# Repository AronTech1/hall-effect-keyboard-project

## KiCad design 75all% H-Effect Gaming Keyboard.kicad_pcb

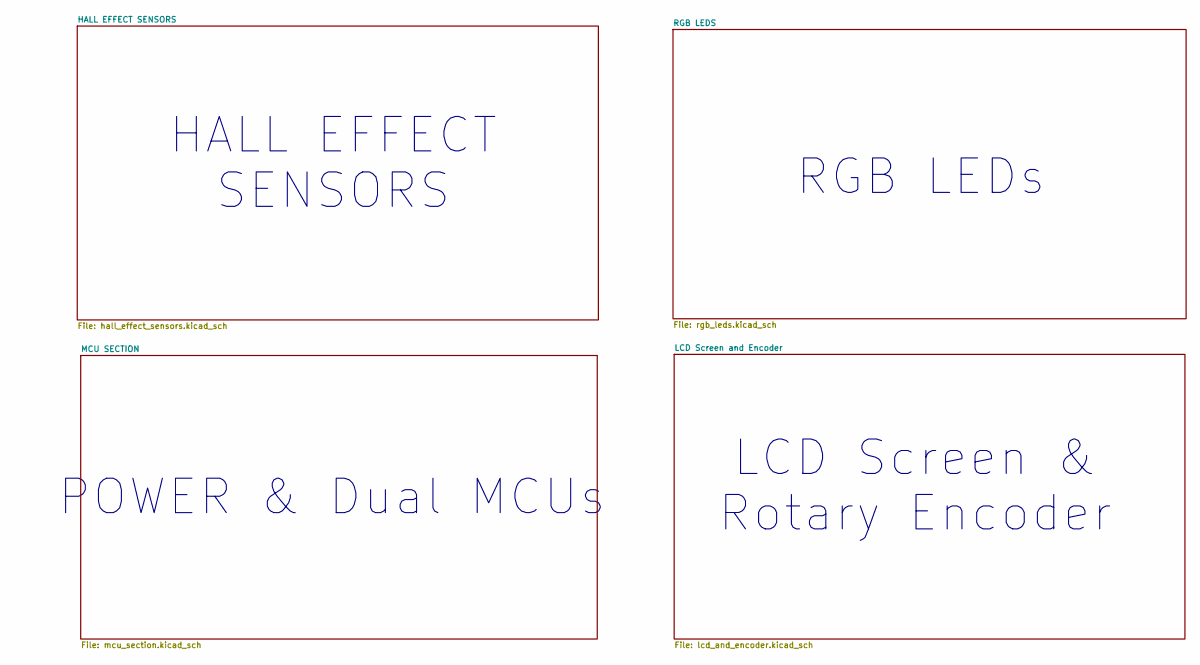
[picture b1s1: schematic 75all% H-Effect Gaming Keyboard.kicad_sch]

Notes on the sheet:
LCD Screen & Rotary Encoder
HALL EFFECT SENSORS
POWER & Dual MCUs
RGB LEDs

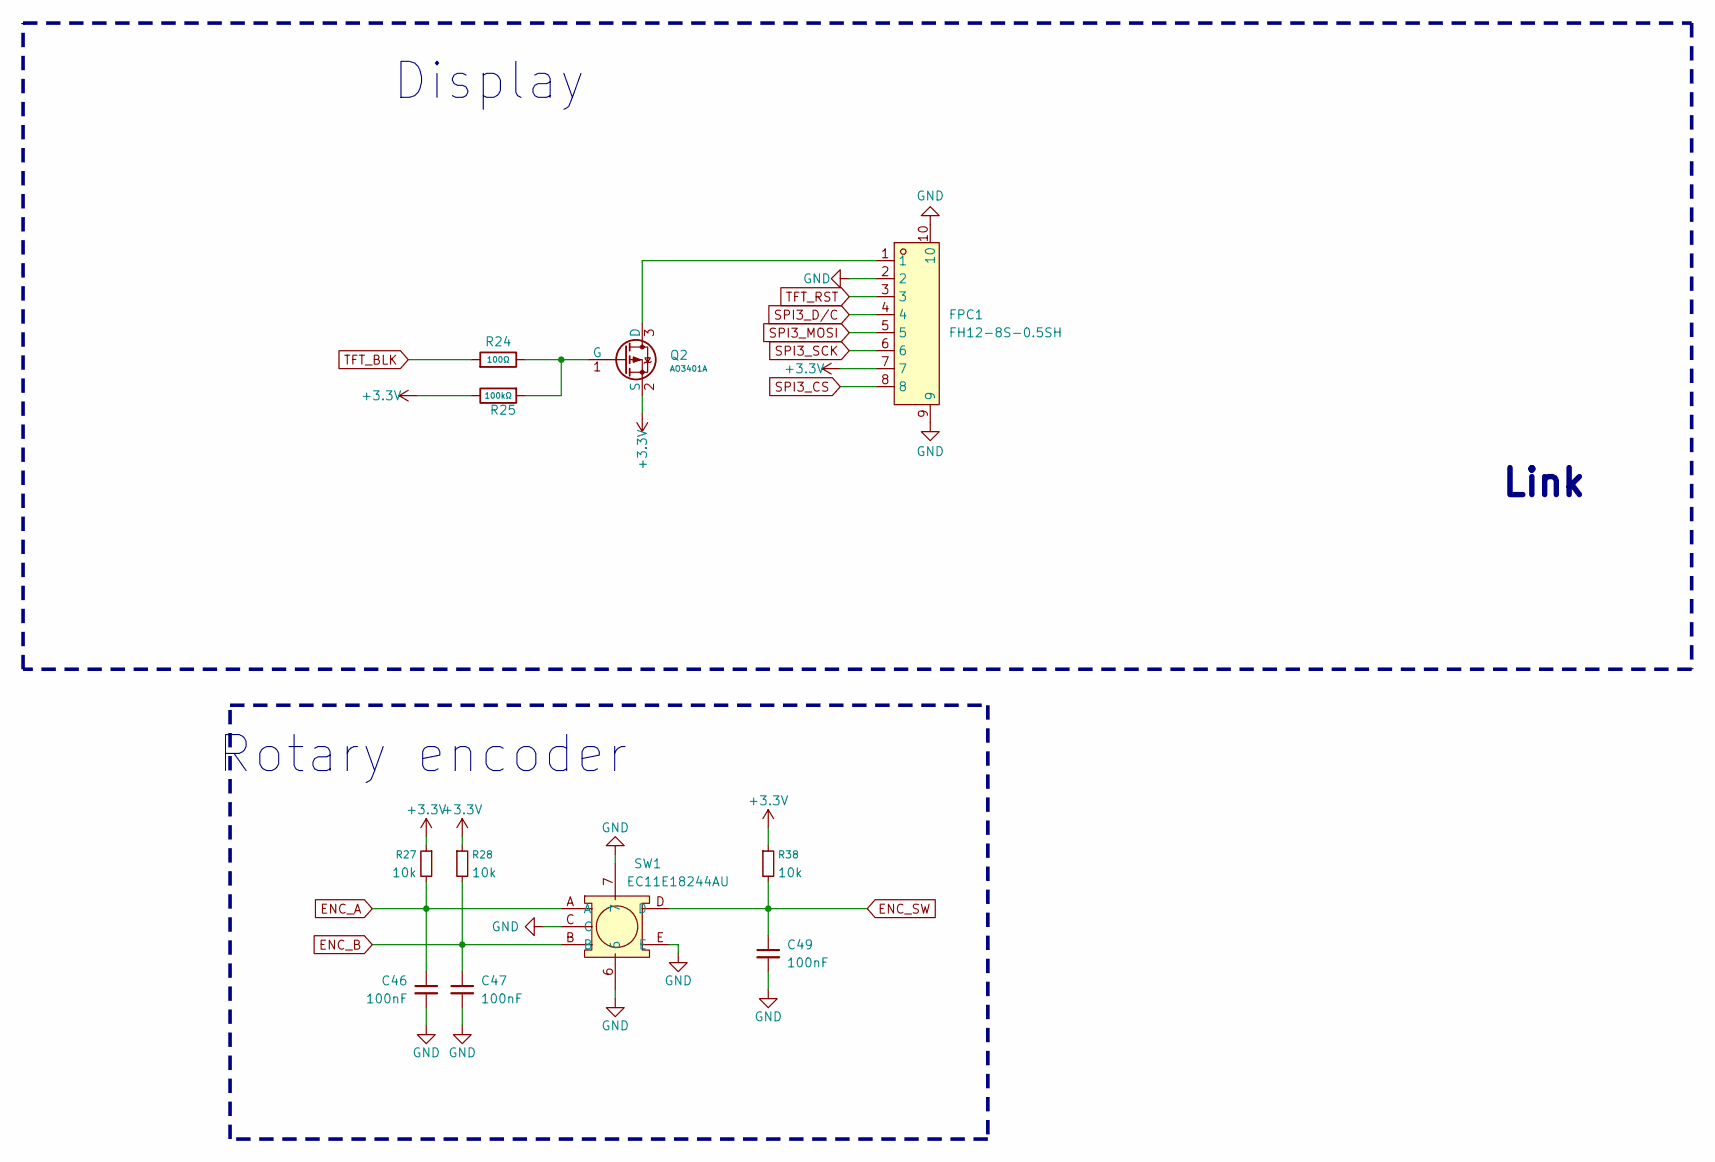
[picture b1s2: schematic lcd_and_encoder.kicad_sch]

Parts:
C46, C47, C49: 100nF; C_0402_1005Metric; JLCPCB Part # C307331
FPC1: FH12-8S-0.5SH; FPC-SMD_8P-P0.50_FH12S-8S-0.5SH-55; MPN FH12-8S-0.5SH(55); LCSC Part C597995
Q2: AO3401A; Q_SOT-23; Part AO3401A; LCSC C15127
R24: 100Ω; R_0603; Overload Voltage (Max) 75V; Tolerance ±1%; Part 0603WAF1000T5E; LCSC C22775
R25: 100kΩ; R_0603; Overload Voltage (Max) 75V; Tolerance ±1%; Part 0603WAF1003T5E; LCSC C25803
R27, R28, R38: 10k; R_0402_1005Metric; JLCPCB Part # C173683
SW1: EC11E18244AU; SW-TH_EC11XXXXXXXX; MPN EC11E18244AU; JLCPCB Part # C202365

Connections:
+3.3V: FPC1.7, Q2.2 (S), R25.2, R27.1, R28.1, R38.1; also elsewhere on the board
ENC_A: C46.1, R27.2, SW1.A; also elsewhere on the board
ENC_B: C47.1, R28.2, SW1.B; also elsewhere on the board
ENC_SW: C49.1, R38.2, SW1.D; also elsewhere on the board
GND: C46.2, C47.2, C49.2, FPC1.2, FPC1.9, FPC1.10, SW1.6, SW1.7, SW1.C, SW1.E; also elsewhere on the board
unnamed: FPC1.1, Q2.3 (D)
unnamed: Q2.1 (G), R24.2, R25.1
SPI3_CS: FPC1.8; also elsewhere on the board
SPI3_D/C: FPC1.4; also elsewhere on the board
SPI3_MOSI: FPC1.5; also elsewhere on the board
SPI3_SCK: FPC1.6; also elsewhere on the board
TFT_BLK: R24.1; also elsewhere on the board
TFT_RST: FPC1.3; also elsewhere on the board

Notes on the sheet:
Link
Display
Rotary encoder

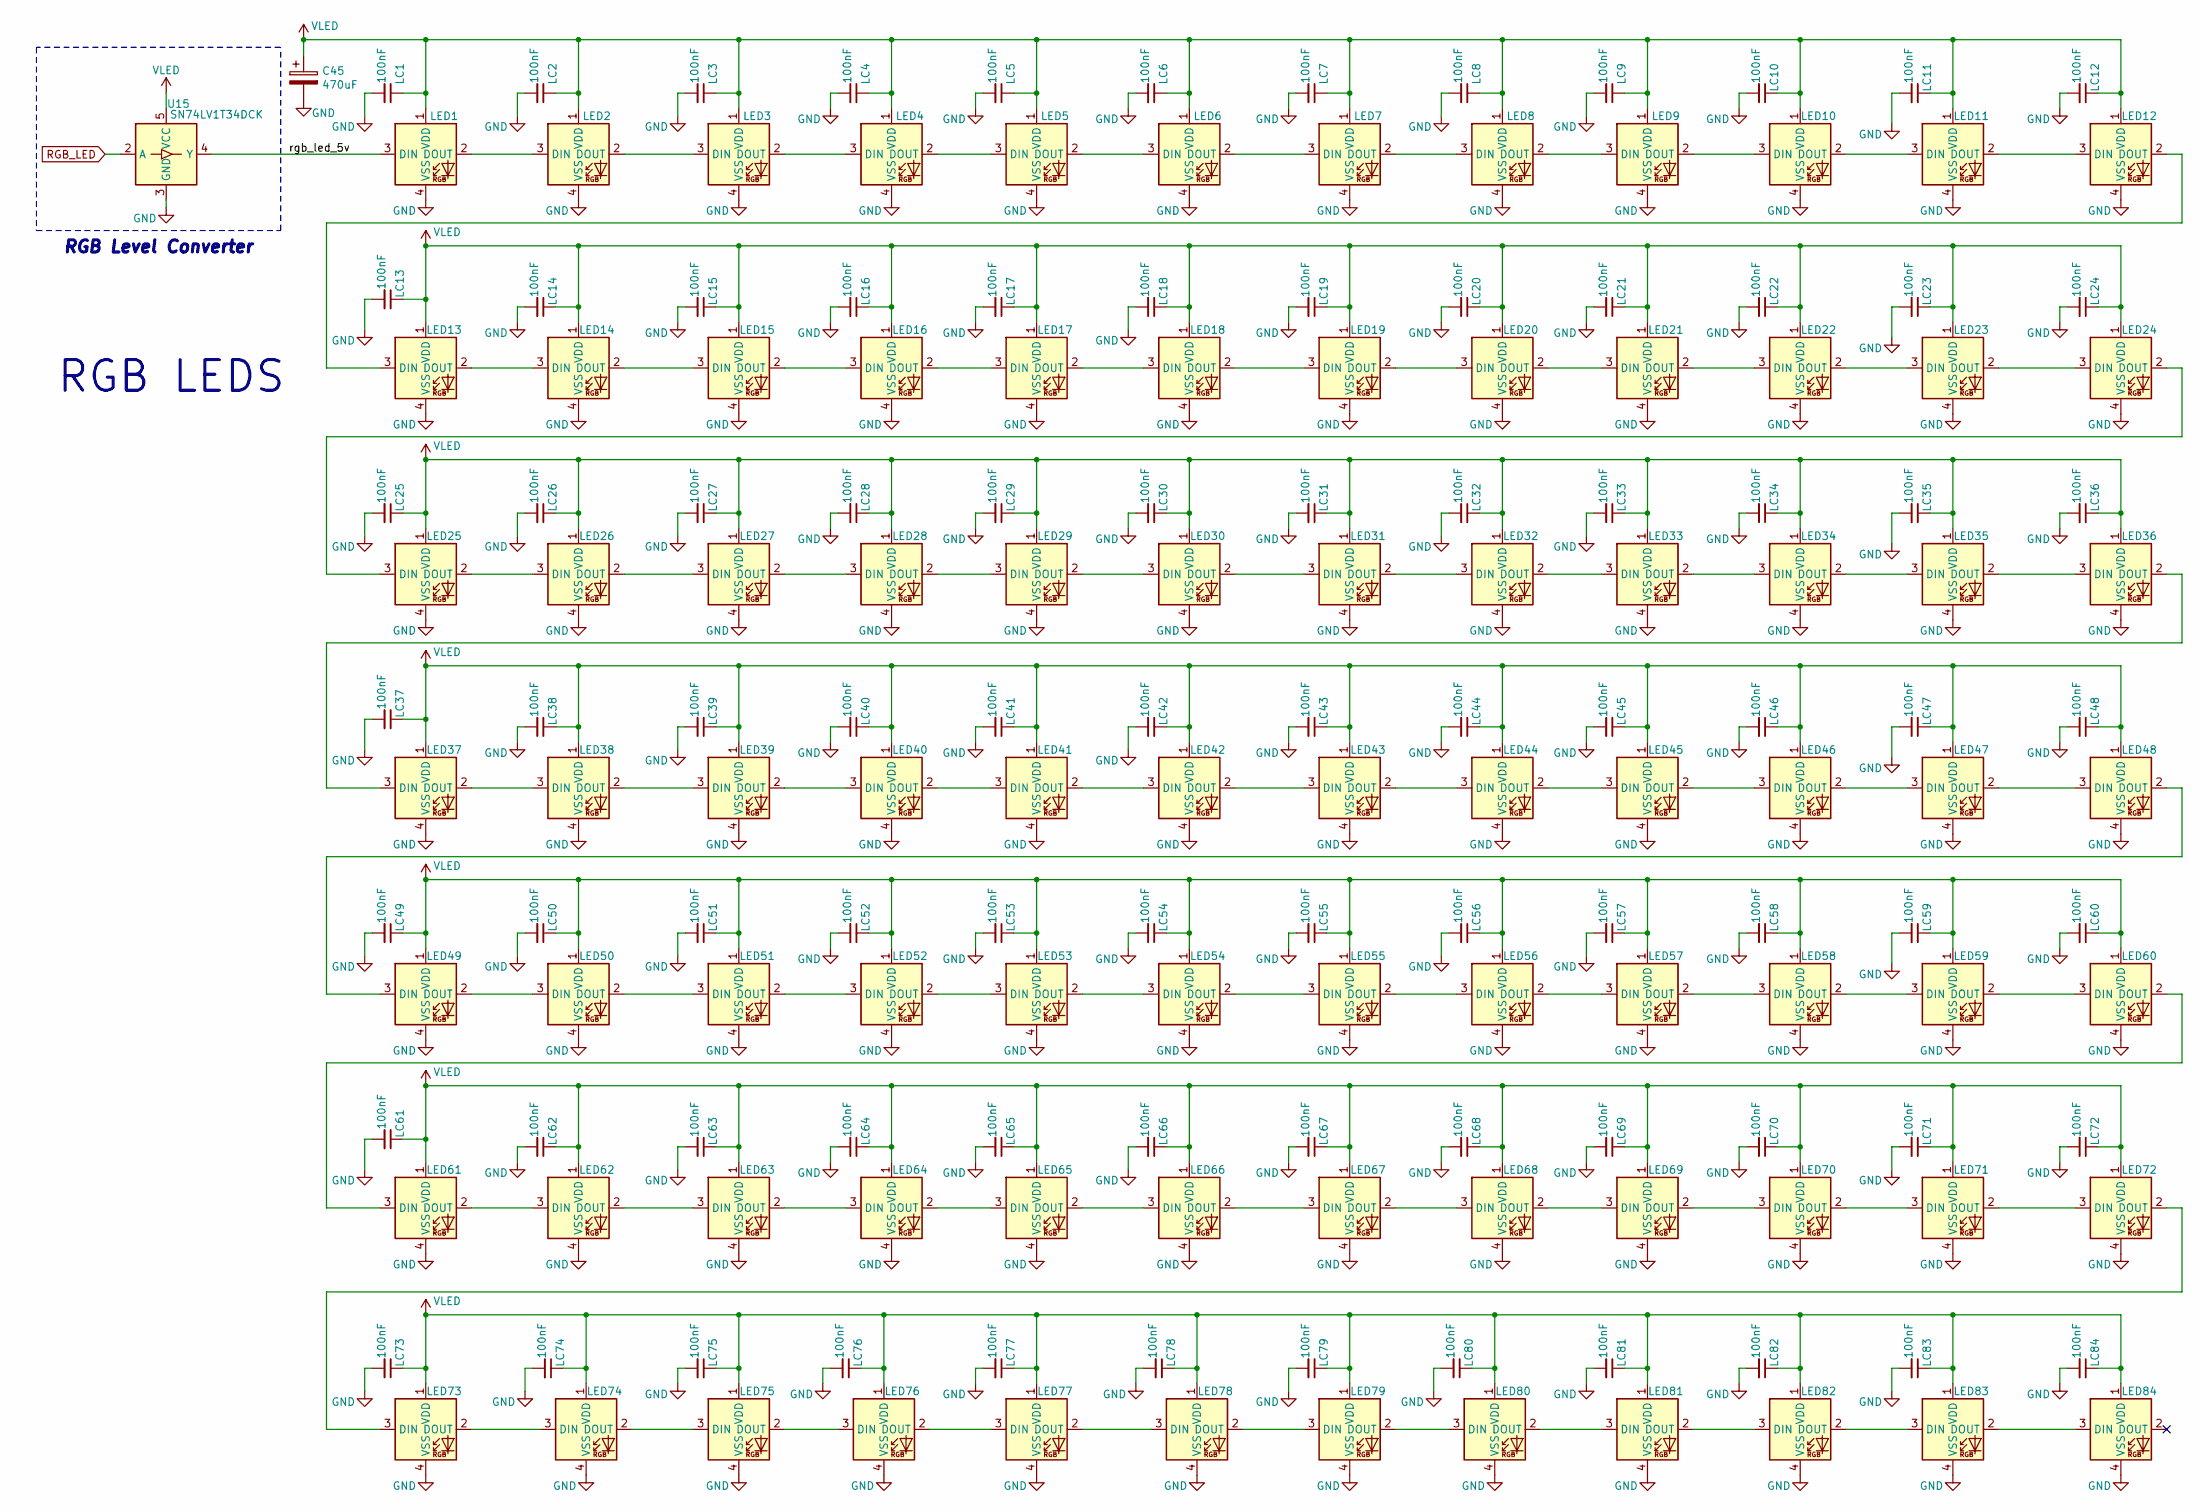
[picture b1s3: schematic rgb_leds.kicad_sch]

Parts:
C45: 470uF; CP_EIA-7343-31_Kemet-D; MFR.Part # TAJD477K006RNJ; JLCPCB Part # C7229
LC1, LC2, LC3, LC4, LC5, LC6, LC7, LC8, LC9, LC10, LC11, LC12, LC13, LC14, LC15, LC16, LC17, LC18, LC19, LC20, LC21, LC22, LC23, LC24, LC25, LC26, LC27, LC28, LC29, LC30, LC31, LC32, LC33, LC34, LC35, LC36, LC37, LC38, LC39, LC40, LC41, LC42, LC43, LC44, LC45, LC46, LC47, LC48, LC49, LC50, LC51, LC52, LC53, LC54, LC55, LC56, LC57, LC58, LC59, LC60, LC61, LC62, LC63, LC64, LC65, LC66, LC67, LC68, LC69, LC70, LC71, LC72, LC73, LC74, LC75, LC76, LC77, LC78, LC79, LC80, LC81, LC82, LC83, LC84: 100nF; C_0402_1005Metric; LCSC C1525
LED1, LED2, LED3, LED4, LED5, LED6, LED7, LED8, LED9, LED10, LED11, LED12, LED13, LED14, LED15, LED16, LED17, LED18, LED19, LED20, LED21, LED22, LED23, LED24, LED25, LED26, LED27, LED28, LED29, LED30, LED31, LED32, LED33, LED34, LED35, LED36, LED37, LED38, LED39, LED40, LED41, LED42, LED43, LED44, LED45, LED46, LED47, LED48, LED49, LED50, LED51, LED52, LED53, LED54, LED55, LED56, LED57, LED58, LED59, LED60, LED61, LED62, LED63, LED64, LED65, LED66, LED67, LED68, LED69, LED70, LED71, LED72, LED73, LED74, LED75, LED76, LED77, LED78, LED79, LED80, LED81, LED82, LED83, LED84: MX_SK6812MINI-E; LED_MX_6028R; LCSC C5149201
U15: SN74LV1T34DCK; SOT-353_SC-70-5; LCSC C48543212

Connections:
/RGB LEDS/rgb_led_5v: LED1.3 (DIN), U15.4 (Y)
GND: C45.2, LC1.2, LC2.2, LC3.2, LC4.2, LC5.2, LC6.2, LC7.2, LC8.2, LC9.2, LC10.2, LC11.2, LC12.2, LC13.2, LC14.2, LC15.2, LC16.2, LC17.2, LC18.2, LC19.2, LC20.2, LC21.2, LC22.2, LC23.2, LC24.2, LC25.2, LC26.2, LC27.2, LC28.2, LC29.2, LC30.2, LC31.2, LC32.2, LC33.2, LC34.2, LC35.2, LC36.2, LC37.2, LC38.2, LC39.2, LC40.2, LC41.2, LC42.2, LC43.2, LC44.2, LC45.2, LC46.2, LC47.2, LC48.2, LC49.2, LC50.2, LC51.2, LC52.2, LC53.2, LC54.2, LC55.2, LC56.2, LC57.2, LC58.2, LC59.2, LC60.2, LC61.2, LC62.2, LC63.2, LC64.2, LC65.2, LC66.2, LC67.2, LC68.2, LC69.2, LC70.2, LC71.2, LC72.2, LC73.2, LC74.2, LC75.2, LC76.2, LC77.2, LC78.2, LC79.2, LC80.2, LC81.2, LC82.2, LC83.2, LC84.2, LED1.4 (VSS), LED2.4 (VSS), LED3.4 (VSS), LED4.4 (VSS), LED5.4 (VSS), LED6.4 (VSS), LED7.4 (VSS), LED8.4 (VSS), LED9.4 (VSS), LED10.4 (VSS), LED11.4 (VSS), LED12.4 (VSS), LED13.4 (VSS), LED14.4 (VSS), LED15.4 (VSS), LED16.4 (VSS), LED17.4 (VSS), LED18.4 (VSS), LED19.4 (VSS), LED20.4 (VSS), LED21.4 (VSS), LED22.4 (VSS), LED23.4 (VSS), LED24.4 (VSS), LED25.4 (VSS), LED26.4 (VSS), LED27.4 (VSS), LED28.4 (VSS), LED29.4 (VSS), LED30.4 (VSS), LED31.4 (VSS), LED32.4 (VSS), LED33.4 (VSS), LED34.4 (VSS), LED35.4 (VSS), LED36.4 (VSS), LED37.4 (VSS), LED38.4 (VSS), LED39.4 (VSS), LED40.4 (VSS), LED41.4 (VSS), LED42.4 (VSS), LED43.4 (VSS), LED44.4 (VSS), LED45.4 (VSS), LED46.4 (VSS), LED47.4 (VSS), LED48.4 (VSS), LED49.4 (VSS), LED50.4 (VSS), LED51.4 (VSS), LED52.4 (VSS), LED53.4 (VSS), LED54.4 (VSS), LED55.4 (VSS), LED56.4 (VSS), LED57.4 (VSS), LED58.4 (VSS), LED59.4 (VSS), LED60.4 (VSS), LED61.4 (VSS), LED62.4 (VSS), LED63.4 (VSS), LED64.4 (VSS), LED65.4 (VSS), LED66.4 (VSS), LED67.4 (VSS), LED68.4 (VSS), LED69.4 (VSS), LED70.4 (VSS), LED71.4 (VSS), LED72.4 (VSS), LED73.4 (VSS), LED74.4 (VSS), LED75.4 (VSS), LED76.4 (VSS), LED77.4 (VSS), LED78.4 (VSS), LED79.4 (VSS), LED80.4 (VSS), LED81.4 (VSS), LED82.4 (VSS), LED83.4 (VSS), LED84.4 (VSS), U15.3 (GND); also elsewhere on the board
unnamed: LED1.2 (DOUT), LED2.3 (DIN)
unnamed: LED2.2 (DOUT), LED3.3 (DIN)
unnamed: LED3.2 (DOUT), LED4.3 (DIN)
unnamed: LED4.2 (DOUT), LED5.3 (DIN)
unnamed: LED5.2 (DOUT), LED6.3 (DIN)
unnamed: LED6.2 (DOUT), LED7.3 (DIN)
unnamed: LED7.2 (DOUT), LED8.3 (DIN)
unnamed: LED8.2 (DOUT), LED9.3 (DIN)
unnamed: LED9.2 (DOUT), LED10.3 (DIN)
unnamed: LED10.2 (DOUT), LED11.3 (DIN)
unnamed: LED11.2 (DOUT), LED12.3 (DIN)
unnamed: LED12.2 (DOUT), LED13.3 (DIN)
unnamed: LED13.2 (DOUT), LED14.3 (DIN)
unnamed: LED14.2 (DOUT), LED15.3 (DIN)
unnamed: LED15.2 (DOUT), LED16.3 (DIN)
unnamed: LED16.2 (DOUT), LED17.3 (DIN)
unnamed: LED17.2 (DOUT), LED18.3 (DIN)
unnamed: LED18.2 (DOUT), LED19.3 (DIN)
unnamed: LED19.2 (DOUT), LED20.3 (DIN)
unnamed: LED20.2 (DOUT), LED21.3 (DIN)
unnamed: LED21.2 (DOUT), LED22.3 (DIN)
unnamed: LED22.2 (DOUT), LED23.3 (DIN)
unnamed: LED23.2 (DOUT), LED24.3 (DIN)
unnamed: LED24.2 (DOUT), LED25.3 (DIN)
unnamed: LED25.2 (DOUT), LED26.3 (DIN)
unnamed: LED26.2 (DOUT), LED27.3 (DIN)
unnamed: LED27.2 (DOUT), LED28.3 (DIN)
unnamed: LED28.2 (DOUT), LED29.3 (DIN)
unnamed: LED29.2 (DOUT), LED30.3 (DIN)
unnamed: LED30.2 (DOUT), LED31.3 (DIN)
unnamed: LED31.2 (DOUT), LED32.3 (DIN)
unnamed: LED32.2 (DOUT), LED33.3 (DIN)
unnamed: LED33.2 (DOUT), LED34.3 (DIN)
unnamed: LED34.2 (DOUT), LED35.3 (DIN)
unnamed: LED35.2 (DOUT), LED36.3 (DIN)
unnamed: LED36.2 (DOUT), LED37.3 (DIN)
unnamed: LED37.2 (DOUT), LED38.3 (DIN)
unnamed: LED38.2 (DOUT), LED39.3 (DIN)
unnamed: LED39.2 (DOUT), LED40.3 (DIN)
unnamed: LED40.2 (DOUT), LED41.3 (DIN)
unnamed: LED41.2 (DOUT), LED42.3 (DIN)
unnamed: LED42.2 (DOUT), LED43.3 (DIN)
unnamed: LED43.2 (DOUT), LED44.3 (DIN)
unnamed: LED44.2 (DOUT), LED45.3 (DIN)
unnamed: LED45.2 (DOUT), LED46.3 (DIN)
unnamed: LED46.2 (DOUT), LED47.3 (DIN)
unnamed: LED47.2 (DOUT), LED48.3 (DIN)
unnamed: LED48.2 (DOUT), LED49.3 (DIN)
unnamed: LED49.2 (DOUT), LED50.3 (DIN)
unnamed: LED50.2 (DOUT), LED51.3 (DIN)
unnamed: LED51.2 (DOUT), LED52.3 (DIN)
unnamed: LED52.2 (DOUT), LED53.3 (DIN)
unnamed: LED53.2 (DOUT), LED54.3 (DIN)
unnamed: LED54.2 (DOUT), LED55.3 (DIN)
unnamed: LED55.2 (DOUT), LED56.3 (DIN)
unnamed: LED56.2 (DOUT), LED57.3 (DIN)
unnamed: LED57.2 (DOUT), LED58.3 (DIN)
unnamed: LED58.2 (DOUT), LED59.3 (DIN)
unnamed: LED59.2 (DOUT), LED60.3 (DIN)
unnamed: LED60.2 (DOUT), LED61.3 (DIN)
unnamed: LED61.2 (DOUT), LED62.3 (DIN)
unnamed: LED62.2 (DOUT), LED63.3 (DIN)
unnamed: LED63.2 (DOUT), LED64.3 (DIN)
unnamed: LED64.2 (DOUT), LED65.3 (DIN)
unnamed: LED65.2 (DOUT), LED66.3 (DIN)
unnamed: LED66.2 (DOUT), LED67.3 (DIN)
unnamed: LED67.2 (DOUT), LED68.3 (DIN)
unnamed: LED68.2 (DOUT), LED69.3 (DIN)
unnamed: LED69.2 (DOUT), LED70.3 (DIN)
unnamed: LED70.2 (DOUT), LED71.3 (DIN)
unnamed: LED71.2 (DOUT), LED72.3 (DIN)
unnamed: LED72.2 (DOUT), LED73.3 (DIN)
unnamed: LED73.2 (DOUT), LED74.3 (DIN)
unnamed: LED74.2 (DOUT), LED75.3 (DIN)
unnamed: LED75.2 (DOUT), LED76.3 (DIN)
unnamed: LED76.2 (DOUT), LED77.3 (DIN)
unnamed: LED77.2 (DOUT), LED78.3 (DIN)
unnamed: LED78.2 (DOUT), LED79.3 (DIN)
unnamed: LED79.2 (DOUT), LED80.3 (DIN)
unnamed: LED80.2 (DOUT), LED81.3 (DIN)
unnamed: LED81.2 (DOUT), LED82.3 (DIN)
unnamed: LED82.2 (DOUT), LED83.3 (DIN)
unnamed: LED83.2 (DOUT), LED84.3 (DIN)
RGB_LED: U15.2 (A); also elsewhere on the board
VLED: C45.1, LC1.1, LC2.1, LC3.1, LC4.1, LC5.1, LC6.1, LC7.1, LC8.1, LC9.1, LC10.1, LC11.1, LC12.1, LC13.1, LC14.1, LC15.1, LC16.1, LC17.1, LC18.1, LC19.1, LC20.1, LC21.1, LC22.1, LC23.1, LC24.1, LC25.1, LC26.1, LC27.1, LC28.1, LC29.1, LC30.1, LC31.1, LC32.1, LC33.1, LC34.1, LC35.1, LC36.1, LC37.1, LC38.1, LC39.1, LC40.1, LC41.1, LC42.1, LC43.1, LC44.1, LC45.1, LC46.1, LC47.1, LC48.1, LC49.1, LC50.1, LC51.1, LC52.1, LC53.1, LC54.1, LC55.1, LC56.1, LC57.1, LC58.1, LC59.1, LC60.1, LC61.1, LC62.1, LC63.1, LC64.1, LC65.1, LC66.1, LC67.1, LC68.1, LC69.1, LC70.1, LC71.1, LC72.1, LC73.1, LC74.1, LC75.1, LC76.1, LC77.1, LC78.1, LC79.1, LC80.1, LC81.1, LC82.1, LC83.1, LC84.1, LED1.1 (VDD), LED2.1 (VDD), LED3.1 (VDD), LED4.1 (VDD), LED5.1 (VDD), LED6.1 (VDD), LED7.1 (VDD), LED8.1 (VDD), LED9.1 (VDD), LED10.1 (VDD), LED11.1 (VDD), LED12.1 (VDD), LED13.1 (VDD), LED14.1 (VDD), LED15.1 (VDD), LED16.1 (VDD), LED17.1 (VDD), LED18.1 (VDD), LED19.1 (VDD), LED20.1 (VDD), LED21.1 (VDD), LED22.1 (VDD), LED23.1 (VDD), LED24.1 (VDD), LED25.1 (VDD), LED26.1 (VDD), LED27.1 (VDD), LED28.1 (VDD), LED29.1 (VDD), LED30.1 (VDD), LED31.1 (VDD), LED32.1 (VDD), LED33.1 (VDD), LED34.1 (VDD), LED35.1 (VDD), LED36.1 (VDD), LED37.1 (VDD), LED38.1 (VDD), LED39.1 (VDD), LED40.1 (VDD), LED41.1 (VDD), LED42.1 (VDD), LED43.1 (VDD), LED44.1 (VDD), LED45.1 (VDD), LED46.1 (VDD), LED47.1 (VDD), LED48.1 (VDD), LED49.1 (VDD), LED50.1 (VDD), LED51.1 (VDD), LED52.1 (VDD), LED53.1 (VDD), LED54.1 (VDD), LED55.1 (VDD), LED56.1 (VDD), LED57.1 (VDD), LED58.1 (VDD), LED59.1 (VDD), LED60.1 (VDD), LED61.1 (VDD), LED62.1 (VDD), LED63.1 (VDD), LED64.1 (VDD), LED65.1 (VDD), LED66.1 (VDD), LED67.1 (VDD), LED68.1 (VDD), LED69.1 (VDD), LED70.1 (VDD), LED71.1 (VDD), LED72.1 (VDD), LED73.1 (VDD), LED74.1 (VDD), LED75.1 (VDD), LED76.1 (VDD), LED77.1 (VDD), LED78.1 (VDD), LED79.1 (VDD), LED80.1 (VDD), LED81.1 (VDD), LED82.1 (VDD), LED83.1 (VDD), LED84.1 (VDD), U15.5 (VCC); also elsewhere on the board

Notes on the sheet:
RGB Level Converter
RGB LEDS

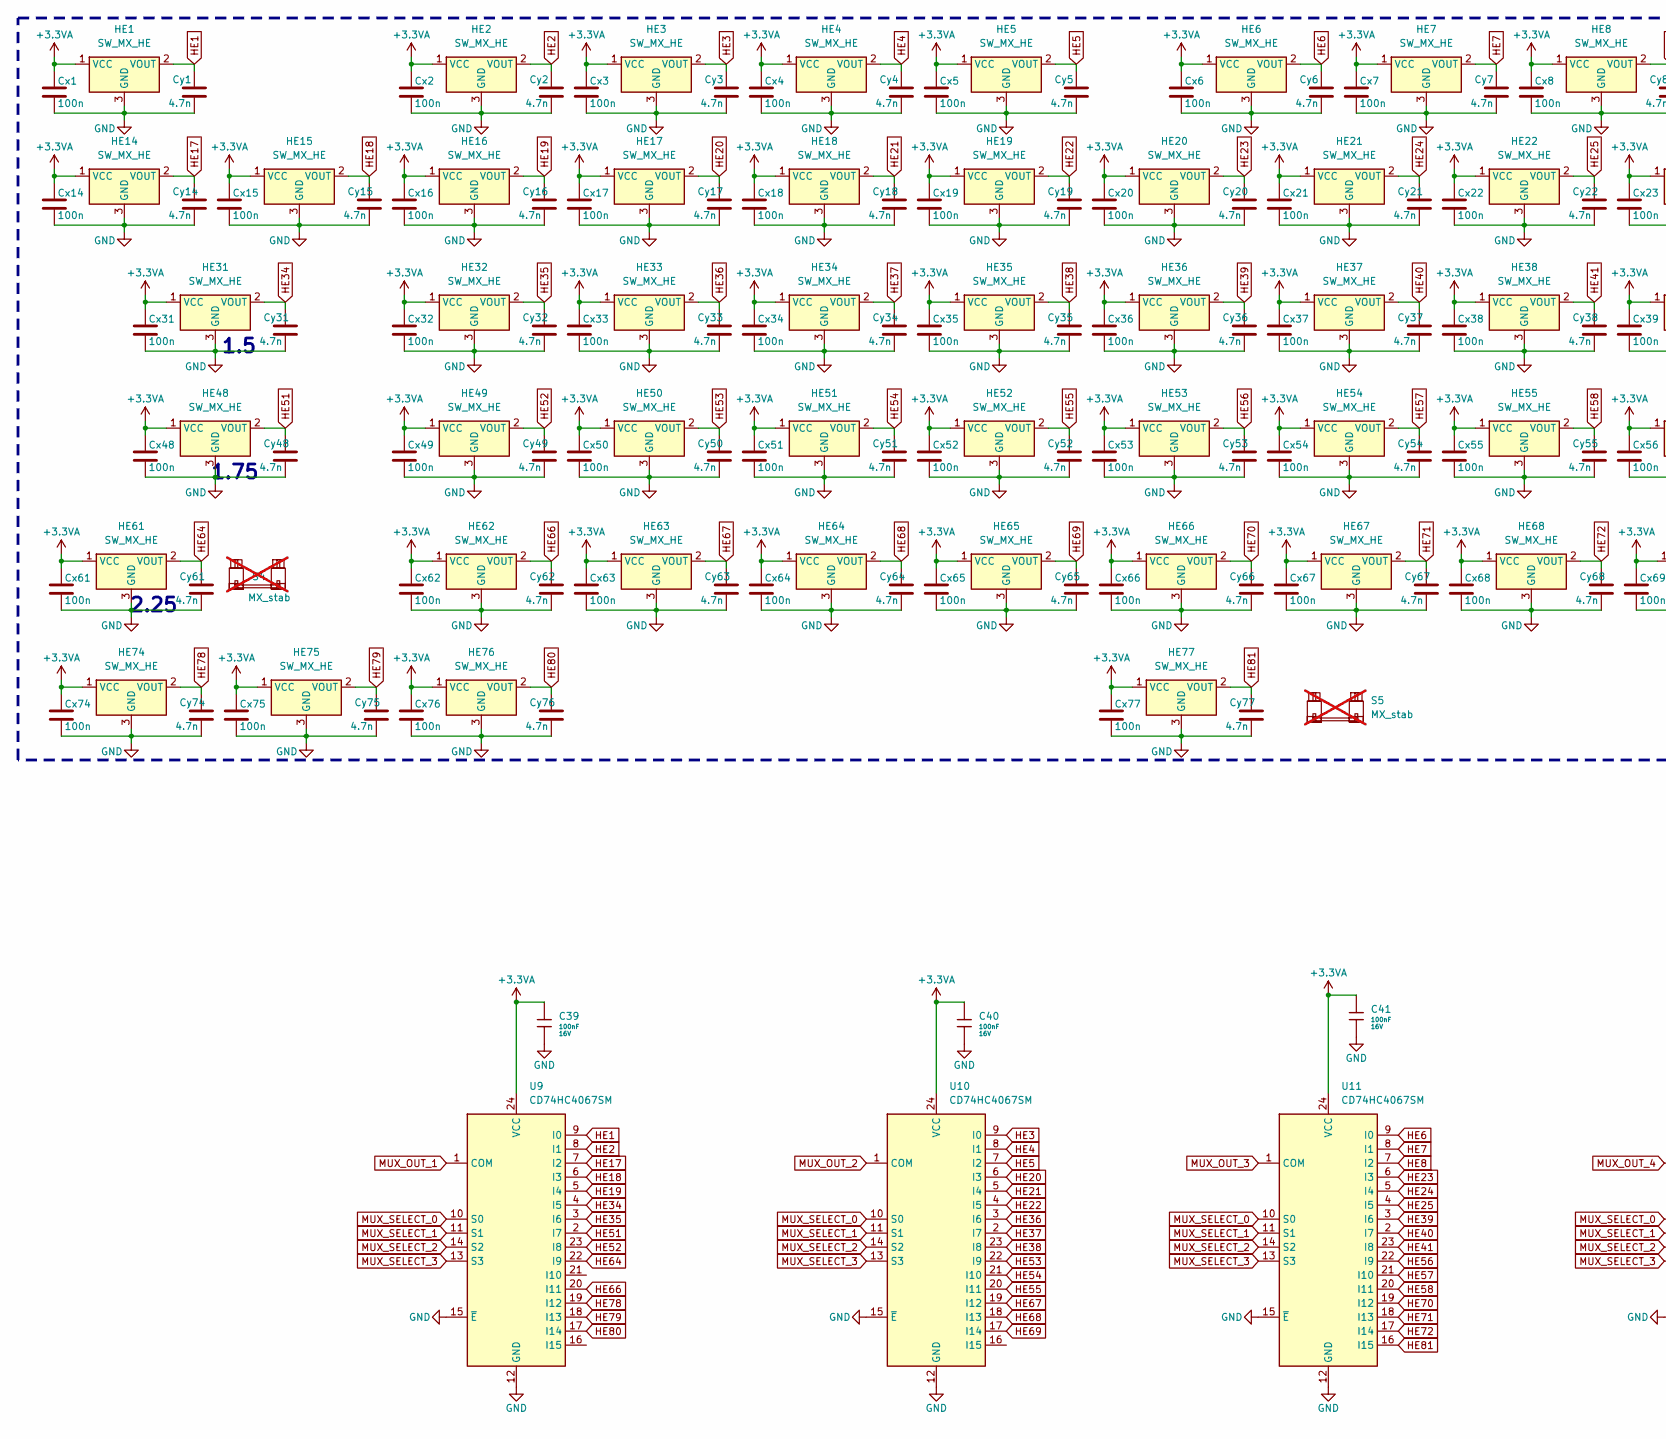
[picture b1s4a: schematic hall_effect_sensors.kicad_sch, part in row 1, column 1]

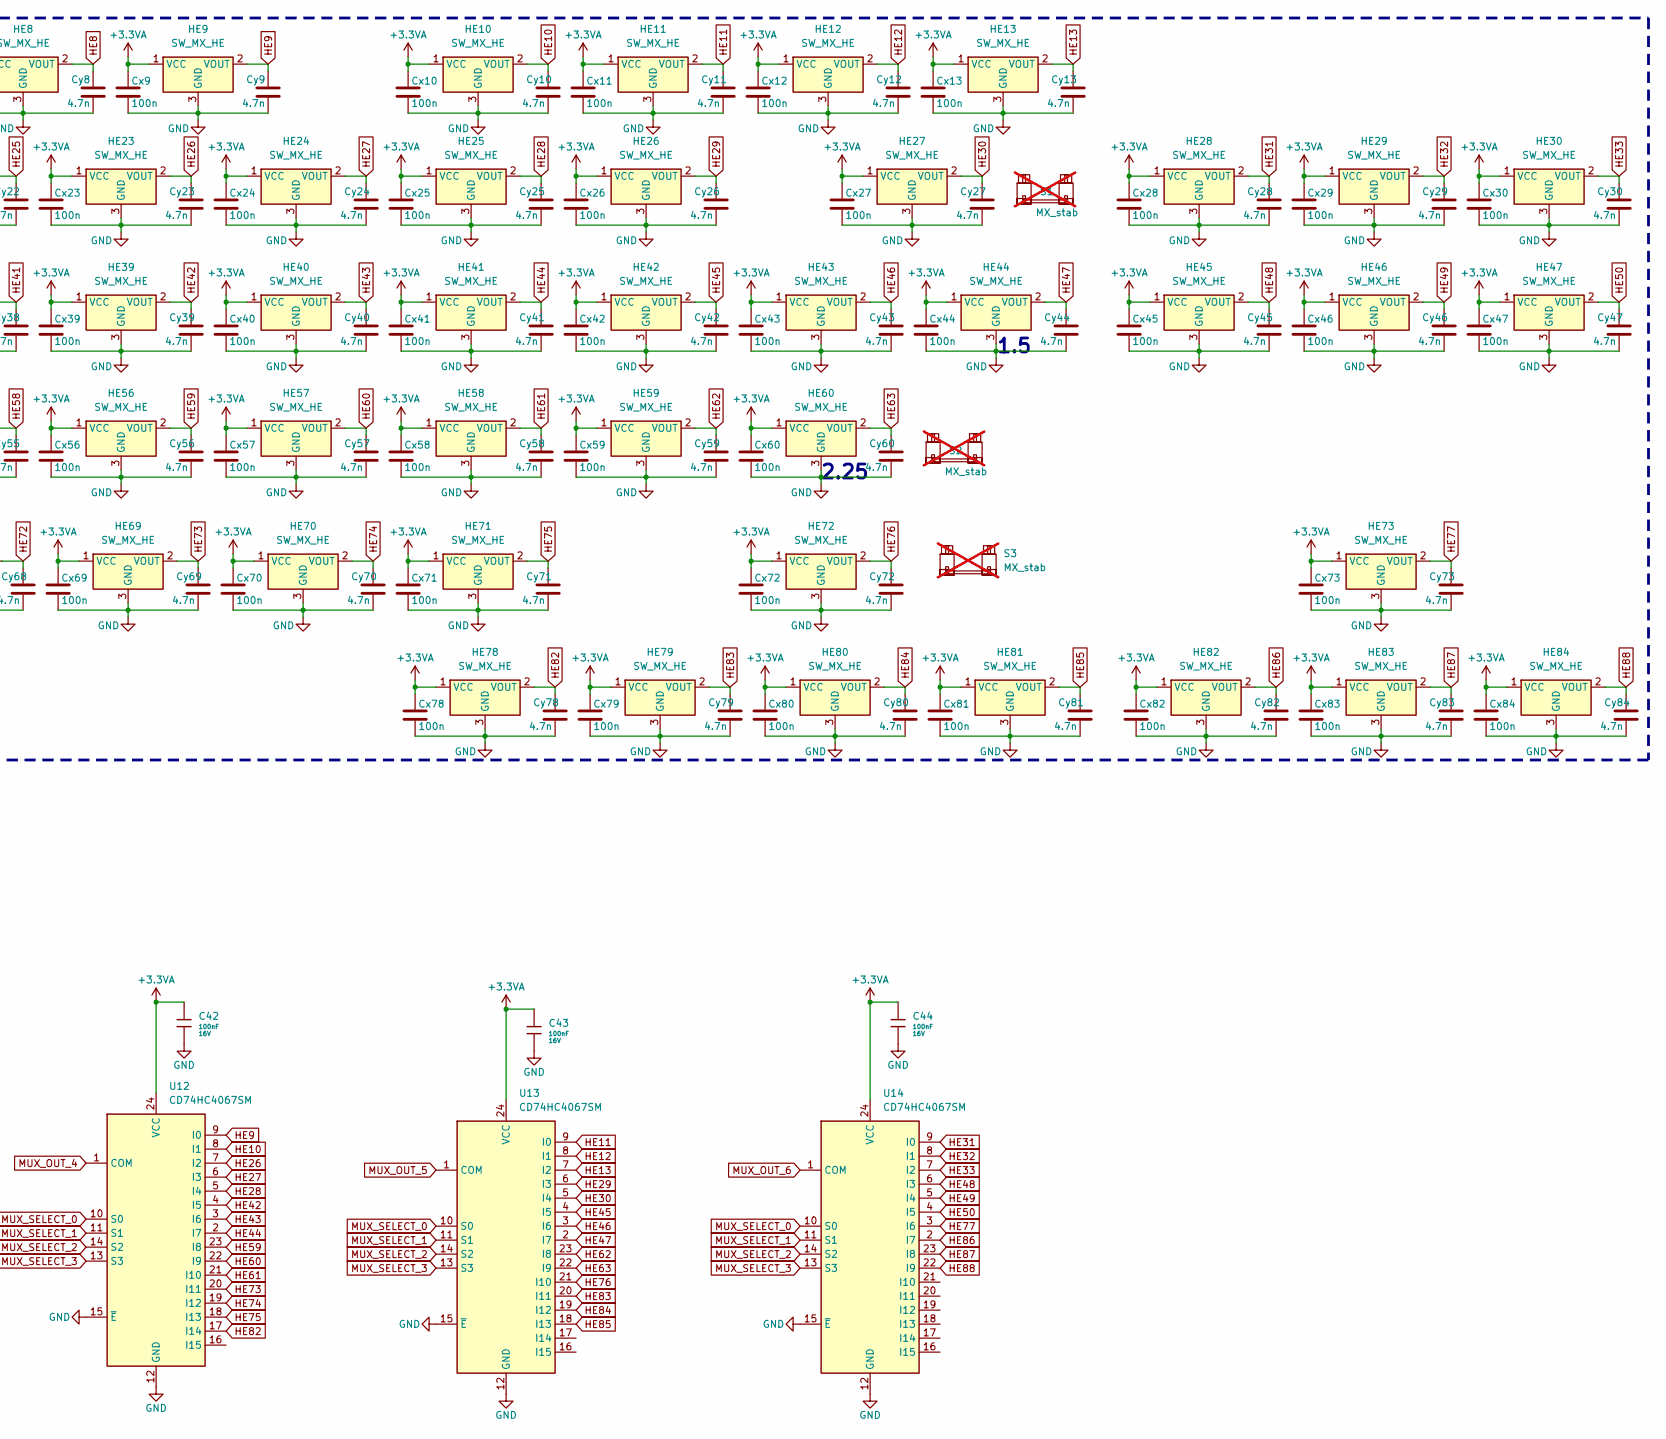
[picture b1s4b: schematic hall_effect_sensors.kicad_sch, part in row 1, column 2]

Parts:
C39, C40, C41, C42, C43, C44: 100nF; C_0402; Voltage Rated 16V; Tolerance ±10%; Part CL05B104KO5NNNC; LCSC C1525
Cx1, Cx2, Cx3, Cx4, Cx5, Cx6, Cx7, Cx8, Cx9, Cx10, Cx11, Cx12, Cx13, Cx14, Cx15, Cx16, Cx17, Cx18, Cx19, Cx20, Cx21, Cx22, Cx23, Cx24, Cx25, Cx26, Cx27, Cx28, Cx29, Cx30, Cx31, Cx32, Cx33, Cx34, Cx35, Cx36, Cx37, Cx38, Cx39, Cx40, Cx41, Cx42, Cx43, Cx44, Cx45, Cx46, Cx47, Cx48, Cx49, Cx50, Cx51, Cx52, Cx53, Cx54, Cx55, Cx56, Cx57, Cx58, Cx59, Cx60, Cx61, Cx62, Cx63, Cx64, Cx65, Cx66, Cx67, Cx68, Cx69, Cx70, Cx71, Cx72, Cx73, Cx74, Cx75, Cx76, Cx77, Cx78, Cx79, Cx80, Cx81, Cx82, Cx83, Cx84: 100n; C_0402_1005Metric
Cy1, Cy2, Cy3, Cy4, Cy5, Cy6, Cy7, Cy8, Cy9, Cy10, Cy11, Cy12, Cy13, Cy14, Cy15, Cy16, Cy17, Cy18, Cy19, Cy20, Cy21, Cy22, Cy23, Cy24, Cy25, Cy26, Cy27, Cy28, Cy29, Cy30, Cy31, Cy32, Cy33, Cy34, Cy35, Cy36, Cy37, Cy38, Cy39, Cy40, Cy41, Cy42, Cy43, Cy44, Cy45, Cy46, Cy47, Cy48, Cy49, Cy50, Cy51, Cy52, Cy53, Cy54, Cy55, Cy56, Cy57, Cy58, Cy59, Cy60, Cy61, Cy62, Cy63, Cy64, Cy65, Cy66, Cy67, Cy68, Cy69, Cy70, Cy71, Cy72, Cy73, Cy74, Cy75, Cy76, Cy77, Cy78, Cy79, Cy80, Cy81, Cy82, Cy83, Cy84: 4.7n; C_0402_1005Metric
HE1, HE2, HE3, HE4, HE5, HE6, HE7, HE8, HE9, HE10, HE11, HE12, HE13, HE14, HE15, HE16, HE17, HE18, HE19, HE20, HE21, HE22, HE23, HE24, HE25, HE26, HE27, HE28, HE29, HE30, HE32, HE33, HE34, HE35, HE36, HE37, HE38, HE39, HE40, HE41, HE42, HE43, HE45, HE46, HE47, HE49, HE50, HE51, HE52, HE53, HE54, HE55, HE56, HE57, HE58, HE59, HE60, HE61, HE62, HE63, HE64, HE65, HE66, HE67, HE68, HE69, HE70, HE71, HE72, HE73, HE77, HE82, HE83, HE84: SW_MX_HE; SW_MX_HE_0deg_1u; LCSC C5447698
HE31, HE44: SW_MX_HE; SW_MX_HE_0deg_1.5u; LCSC C5447698
HE48: SW_MX_HE; SW_MX_HE_0deg_1.75u; LCSC C5447698
HE74, HE75, HE76, HE78, HE79, HE80, HE81: SW_MX_HE; SW_MX_HE_0deg_1.25u; LCSC C5447698
S1: MX_stab; STAB_MX_P_2u; not fitted
S2, S4: MX_stab; STAB_MX_2.25u; not fitted
S3: MX_stab; STAB_MX_P_2.75u; not fitted
S5: MX_stab; STAB_MX_P_6.25u; not fitted
U9, U10, U11, U12, U13, U14: CD74HC4067SM; SSOP-24_5.3x8.2mm_P0.65mm

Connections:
+3.3VA: C39.1, C40.1, C41.1, C42.1, C43.1, C44.1, Cx1.1, Cx2.1, Cx3.1, Cx4.1, Cx5.1, Cx6.1, Cx7.1, Cx8.1, Cx9.1, Cx10.1, Cx11.1, Cx12.1, Cx13.1, Cx14.1, Cx15.1, Cx16.1, Cx17.1, Cx18.1, Cx19.1, Cx20.1, Cx21.1, Cx22.1, Cx23.1, Cx24.1, Cx25.1, Cx26.1, Cx27.1, Cx28.1, Cx29.1, Cx30.1, Cx31.1, Cx32.1, Cx33.1, Cx34.1, Cx35.1, Cx36.1, Cx37.1, Cx38.1, Cx39.1, Cx40.1, Cx41.1, Cx42.1, Cx43.1, Cx44.1, Cx45.1, Cx46.1, Cx47.1, Cx48.1, Cx49.1, Cx50.1, Cx51.1, Cx52.1, Cx53.1, Cx54.1, Cx55.1, Cx56.1, Cx57.1, Cx58.1, Cx59.1, Cx60.1, Cx61.1, Cx62.1, Cx63.1, Cx64.1, Cx65.1, Cx66.1, Cx67.1, Cx68.1, Cx69.1, Cx70.1, Cx71.1, Cx72.1, Cx73.1, Cx74.1, Cx75.1, Cx76.1, Cx77.1, Cx78.1, Cx79.1, Cx80.1, Cx81.1, Cx82.1, Cx83.1, Cx84.1, HE1.1 (VCC), HE2.1 (VCC), HE3.1 (VCC), HE4.1 (VCC), HE5.1 (VCC), HE6.1 (VCC), HE7.1 (VCC), HE8.1 (VCC), HE9.1 (VCC), HE10.1 (VCC), HE11.1 (VCC), HE12.1 (VCC), HE13.1 (VCC), HE14.1 (VCC), HE15.1 (VCC), HE16.1 (VCC), HE17.1 (VCC), HE18.1 (VCC), HE19.1 (VCC), HE20.1 (VCC), HE21.1 (VCC), HE22.1 (VCC), HE23.1 (VCC), HE24.1 (VCC), HE25.1 (VCC), HE26.1 (VCC), HE27.1 (VCC), HE28.1 (VCC), HE29.1 (VCC), HE30.1 (VCC), HE31.1 (VCC), HE32.1 (VCC), HE33.1 (VCC), HE34.1 (VCC), HE35.1 (VCC), HE36.1 (VCC), HE37.1 (VCC), HE38.1 (VCC), HE39.1 (VCC), HE40.1 (VCC), HE41.1 (VCC), HE42.1 (VCC), HE43.1 (VCC), HE44.1 (VCC), HE45.1 (VCC), HE46.1 (VCC), HE47.1 (VCC), HE48.1 (VCC), HE49.1 (VCC), HE50.1 (VCC), HE51.1 (VCC), HE52.1 (VCC), HE53.1 (VCC), HE54.1 (VCC), HE55.1 (VCC), HE56.1 (VCC), HE57.1 (VCC), HE58.1 (VCC), HE59.1 (VCC), HE60.1 (VCC), HE61.1 (VCC), HE62.1 (VCC), HE63.1 (VCC), HE64.1 (VCC), HE65.1 (VCC), HE66.1 (VCC), HE67.1 (VCC), HE68.1 (VCC), HE69.1 (VCC), HE70.1 (VCC), HE71.1 (VCC), HE72.1 (VCC), HE73.1 (VCC), HE74.1 (VCC), HE75.1 (VCC), HE76.1 (VCC), HE77.1 (VCC), HE78.1 (VCC), HE79.1 (VCC), HE80.1 (VCC), HE81.1 (VCC), HE82.1 (VCC), HE83.1 (VCC), HE84.1 (VCC), U9.24 (VCC), U10.24 (VCC), U11.24 (VCC), U12.24 (VCC), U13.24 (VCC), U14.24 (VCC); also elsewhere on the board
GND: C39.2, C40.2, C41.2, C42.2, C43.2, C44.2, Cx1.2, Cx2.2, Cx3.2, Cx4.2, Cx5.2, Cx6.2, Cx7.2, Cx8.2, Cx9.2, Cx10.2, Cx11.2, Cx12.2, Cx13.2, Cx14.2, Cx15.2, Cx16.2, Cx17.2, Cx18.2, Cx19.2, Cx20.2, Cx21.2, Cx22.2, Cx23.2, Cx24.2, Cx25.2, Cx26.2, Cx27.2, Cx28.2, Cx29.2, Cx30.2, Cx31.2, Cx32.2, Cx33.2, Cx34.2, Cx35.2, Cx36.2, Cx37.2, Cx38.2, Cx39.2, Cx40.2, Cx41.2, Cx42.2, Cx43.2, Cx44.2, Cx45.2, Cx46.2, Cx47.2, Cx48.2, Cx49.2, Cx50.2, Cx51.2, Cx52.2, Cx53.2, Cx54.2, Cx55.2, Cx56.2, Cx57.2, Cx58.2, Cx59.2, Cx60.2, Cx61.2, Cx62.2, Cx63.2, Cx64.2, Cx65.2, Cx66.2, Cx67.2, Cx68.2, Cx69.2, Cx70.2, Cx71.2, Cx72.2, Cx73.2, Cx74.2, Cx75.2, Cx76.2, Cx77.2, Cx78.2, Cx79.2, Cx80.2, Cx81.2, Cx82.2, Cx83.2, Cx84.2, Cy1.2, Cy2.2, Cy3.2, Cy4.2, Cy5.2, Cy6.2, Cy7.2, Cy8.2, Cy9.2, Cy10.2, Cy11.2, Cy12.2, Cy13.2, Cy14.2, Cy15.2, Cy16.2, Cy17.2, Cy18.2, Cy19.2, Cy20.2, Cy21.2, Cy22.2, Cy23.2, Cy24.2, Cy25.2, Cy26.2, Cy27.2, Cy28.2, Cy29.2, Cy30.2, Cy31.2, Cy32.2, Cy33.2, Cy34.2, Cy35.2, Cy36.2, Cy37.2, Cy38.2, Cy39.2, Cy40.2, Cy41.2, Cy42.2, Cy43.2, Cy44.2, Cy45.2, Cy46.2, Cy47.2, Cy48.2, Cy49.2, Cy50.2, Cy51.2, Cy52.2, Cy53.2, Cy54.2, Cy55.2, Cy56.2, Cy57.2, Cy58.2, Cy59.2, Cy60.2, Cy61.2, Cy62.2, Cy63.2, Cy64.2, Cy65.2, Cy66.2, Cy67.2, Cy68.2, Cy69.2, Cy70.2, Cy71.2, Cy72.2, Cy73.2, Cy74.2, Cy75.2, Cy76.2, Cy77.2, Cy78.2, Cy79.2, Cy80.2, Cy81.2, Cy82.2, Cy83.2, Cy84.2, HE1.3 (GND), HE2.3 (GND), HE3.3 (GND), HE4.3 (GND), HE5.3 (GND), HE6.3 (GND), HE7.3 (GND), HE8.3 (GND), HE9.3 (GND), HE10.3 (GND), HE11.3 (GND), HE12.3 (GND), HE13.3 (GND), HE14.3 (GND), HE15.3 (GND), HE16.3 (GND), HE17.3 (GND), HE18.3 (GND), HE19.3 (GND), HE20.3 (GND), HE21.3 (GND), HE22.3 (GND), HE23.3 (GND), HE24.3 (GND), HE25.3 (GND), HE26.3 (GND), HE27.3 (GND), HE28.3 (GND), HE29.3 (GND), HE30.3 (GND), HE31.3 (GND), HE32.3 (GND), HE33.3 (GND), HE34.3 (GND), HE35.3 (GND), HE36.3 (GND), HE37.3 (GND), HE38.3 (GND), HE39.3 (GND), HE40.3 (GND), HE41.3 (GND), HE42.3 (GND), HE43.3 (GND), HE44.3 (GND), HE45.3 (GND), HE46.3 (GND), HE47.3 (GND), HE48.3 (GND), HE49.3 (GND), HE50.3 (GND), HE51.3 (GND), HE52.3 (GND), HE53.3 (GND), HE54.3 (GND), HE55.3 (GND), HE56.3 (GND), HE57.3 (GND), HE58.3 (GND), HE59.3 (GND), HE60.3 (GND), HE61.3 (GND), HE62.3 (GND), HE63.3 (GND), HE64.3 (GND), HE65.3 (GND), HE66.3 (GND), HE67.3 (GND), HE68.3 (GND), HE69.3 (GND), HE70.3 (GND), HE71.3 (GND), HE72.3 (GND), HE73.3 (GND), HE74.3 (GND), HE75.3 (GND), HE76.3 (GND), HE77.3 (GND), HE78.3 (GND), HE79.3 (GND), HE80.3 (GND), HE81.3 (GND), HE82.3 (GND), HE83.3 (GND), HE84.3 (GND), U9.12 (GND), U9.15 (~E), U10.12 (GND), U10.15 (~E), U11.12 (GND), U11.15 (~E), U12.12 (GND), U12.15 (~E), U13.12 (GND), U13.15 (~E), U14.12 (GND), U14.15 (~E); also elsewhere on the board
HE1: Cy1.1, HE1.2 (VOUT), U9.9 (I0)
HE2: Cy2.1, HE2.2 (VOUT), U9.8 (I1)
HE3: Cy3.1, HE3.2 (VOUT), U10.9 (I0)
HE4: Cy4.1, HE4.2 (VOUT), U10.8 (I1)
HE5: Cy5.1, HE5.2 (VOUT), U10.7 (I2)
HE6: Cy6.1, HE6.2 (VOUT), U11.9 (I0)
HE7: Cy7.1, HE7.2 (VOUT), U11.8 (I1)
HE8: Cy8.1, HE8.2 (VOUT), U11.7 (I2)
HE9: Cy9.1, HE9.2 (VOUT), U12.9 (I0)
HE10: Cy10.1, HE10.2 (VOUT), U12.8 (I1)
HE11: Cy11.1, HE11.2 (VOUT), U13.9 (I0)
HE12: Cy12.1, HE12.2 (VOUT), U13.8 (I1)
HE13: Cy13.1, HE13.2 (VOUT), U13.7 (I2)
HE17: Cy14.1, HE14.2 (VOUT), U9.7 (I2)
HE18: Cy15.1, HE15.2 (VOUT), U9.6 (I3)
HE19: Cy16.1, HE16.2 (VOUT), U9.5 (I4)
HE20: Cy17.1, HE17.2 (VOUT), U10.6 (I3)
HE21: Cy18.1, HE18.2 (VOUT), U10.5 (I4)
HE22: Cy19.1, HE19.2 (VOUT), U10.4 (I5)
HE23: Cy20.1, HE20.2 (VOUT), U11.6 (I3)
HE24: Cy21.1, HE21.2 (VOUT), U11.5 (I4)
HE25: Cy22.1, HE22.2 (VOUT), U11.4 (I5)
HE26: Cy23.1, HE23.2 (VOUT), U12.7 (I2)
HE27: Cy24.1, HE24.2 (VOUT), U12.6 (I3)
HE28: Cy25.1, HE25.2 (VOUT), U12.5 (I4)
HE29: Cy26.1, HE26.2 (VOUT), U13.6 (I3)
HE30: Cy27.1, HE27.2 (VOUT), U13.5 (I4)
HE31: Cy28.1, HE28.2 (VOUT), U14.9 (I0)
HE32: Cy29.1, HE29.2 (VOUT), U14.8 (I1)
HE33: Cy30.1, HE30.2 (VOUT), U14.7 (I2)
HE34: Cy31.1, HE31.2 (VOUT), U9.4 (I5)
HE35: Cy32.1, HE32.2 (VOUT), U9.3 (I6)
HE36: Cy33.1, HE33.2 (VOUT), U10.3 (I6)
HE37: Cy34.1, HE34.2 (VOUT), U10.2 (I7)
HE38: Cy35.1, HE35.2 (VOUT), U10.23 (I8)
HE39: Cy36.1, HE36.2 (VOUT), U11.3 (I6)
HE40: Cy37.1, HE37.2 (VOUT), U11.2 (I7)
HE41: Cy38.1, HE38.2 (VOUT), U11.23 (I8)
HE42: Cy39.1, HE39.2 (VOUT), U12.4 (I5)
HE43: Cy40.1, HE40.2 (VOUT), U12.3 (I6)
HE44: Cy41.1, HE41.2 (VOUT), U12.2 (I7)
HE45: Cy42.1, HE42.2 (VOUT), U13.4 (I5)
HE46: Cy43.1, HE43.2 (VOUT), U13.3 (I6)
HE47: Cy44.1, HE44.2 (VOUT), U13.2 (I7)
HE48: Cy45.1, HE45.2 (VOUT), U14.6 (I3)
HE49: Cy46.1, HE46.2 (VOUT), U14.5 (I4)
HE50: Cy47.1, HE47.2 (VOUT), U14.4 (I5)
HE51: Cy48.1, HE48.2 (VOUT), U9.2 (I7)
HE52: Cy49.1, HE49.2 (VOUT), U9.23 (I8)
HE53: Cy50.1, HE50.2 (VOUT), U10.22 (I9)
HE54: Cy51.1, HE51.2 (VOUT), U10.21 (I10)
HE55: Cy52.1, HE52.2 (VOUT), U10.20 (I11)
HE56: Cy53.1, HE53.2 (VOUT), U11.22 (I9)
HE57: Cy54.1, HE54.2 (VOUT), U11.21 (I10)
HE58: Cy55.1, HE55.2 (VOUT), U11.20 (I11)
HE59: Cy56.1, HE56.2 (VOUT), U12.23 (I8)
HE60: Cy57.1, HE57.2 (VOUT), U12.22 (I9)
HE61: Cy58.1, HE58.2 (VOUT), U12.21 (I10)
HE62: Cy59.1, HE59.2 (VOUT), U13.23 (I8)
HE63: Cy60.1, HE60.2 (VOUT), U13.22 (I9)
HE64: Cy61.1, HE61.2 (VOUT), U9.22 (I9)
HE66: Cy62.1, HE62.2 (VOUT), U9.20 (I11)
HE67: Cy63.1, HE63.2 (VOUT), U10.19 (I12)
HE68: Cy64.1, HE64.2 (VOUT), U10.18 (I13)
HE69: Cy65.1, HE65.2 (VOUT), U10.17 (I14)
HE70: Cy66.1, HE66.2 (VOUT), U11.19 (I12)
HE71: Cy67.1, HE67.2 (VOUT), U11.18 (I13)
HE72: Cy68.1, HE68.2 (VOUT), U11.17 (I14)
HE73: Cy69.1, HE69.2 (VOUT), U12.20 (I11)
HE74: Cy70.1, HE70.2 (VOUT), U12.19 (I12)
HE75: Cy71.1, HE71.2 (VOUT), U12.18 (I13)
HE76: Cy72.1, HE72.2 (VOUT), U13.21 (I10)
HE77: Cy73.1, HE73.2 (VOUT), U14.3 (I6)
HE78: Cy74.1, HE74.2 (VOUT), U9.19 (I12)
HE79: Cy75.1, HE75.2 (VOUT), U9.18 (I13)
HE80: Cy76.1, HE76.2 (VOUT), U9.17 (I14)
HE81: Cy77.1, HE77.2 (VOUT), U11.16 (I15)
HE82: Cy78.1, HE78.2 (VOUT), U12.17 (I14)
HE83: Cy79.1, HE79.2 (VOUT), U13.20 (I11)
HE84: Cy80.1, HE80.2 (VOUT), U13.19 (I12)
HE85: Cy81.1, HE81.2 (VOUT), U13.18 (I13)
HE86: Cy82.1, HE82.2 (VOUT), U14.2 (I7)
HE87: Cy83.1, HE83.2 (VOUT), U14.23 (I8)
HE88: Cy84.1, HE84.2 (VOUT), U14.22 (I9)
MUX_OUT_1: U9.1 (COM); also elsewhere on the board
MUX_OUT_2: U10.1 (COM); also elsewhere on the board
MUX_OUT_3: U11.1 (COM); also elsewhere on the board
MUX_OUT_4: U12.1 (COM); also elsewhere on the board
MUX_OUT_5: U13.1 (COM); also elsewhere on the board
MUX_OUT_6: U14.1 (COM); also elsewhere on the board
MUX_SELECT_0: U9.10 (S0), U10.10 (S0), U11.10 (S0), U12.10 (S0), U13.10 (S0), U14.10 (S0); also elsewhere on the board
MUX_SELECT_1: U9.11 (S1), U10.11 (S1), U11.11 (S1), U12.11 (S1), U13.11 (S1), U14.11 (S1); also elsewhere on the board
MUX_SELECT_2: U9.14 (S2), U10.14 (S2), U11.14 (S2), U12.14 (S2), U13.14 (S2), U14.14 (S2); also elsewhere on the board
MUX_SELECT_3: U9.13 (S3), U10.13 (S3), U11.13 (S3), U12.13 (S3), U13.13 (S3), U14.13 (S3); also elsewhere on the board

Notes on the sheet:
1.75
2.25
1.5
